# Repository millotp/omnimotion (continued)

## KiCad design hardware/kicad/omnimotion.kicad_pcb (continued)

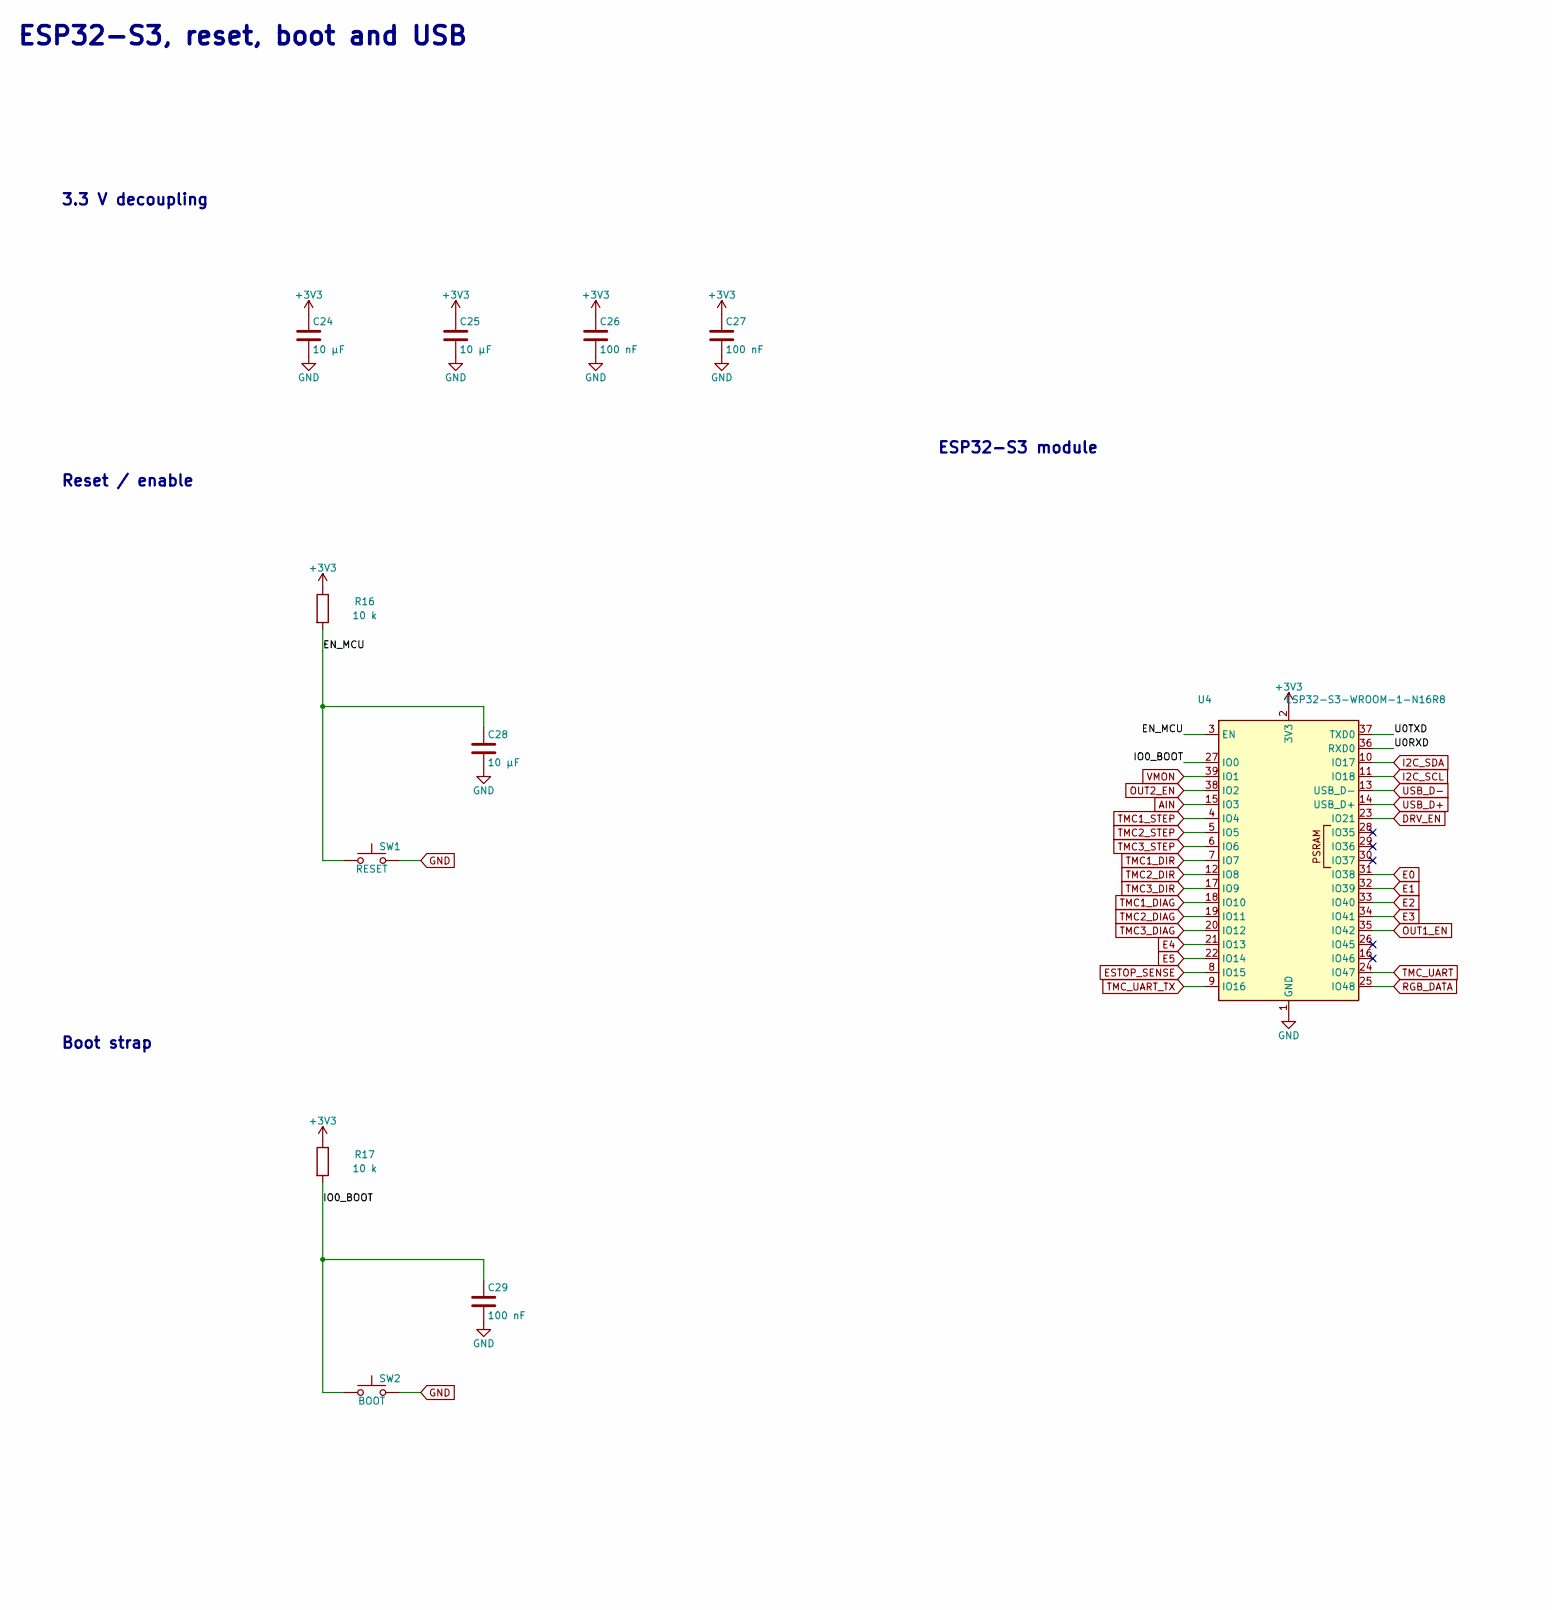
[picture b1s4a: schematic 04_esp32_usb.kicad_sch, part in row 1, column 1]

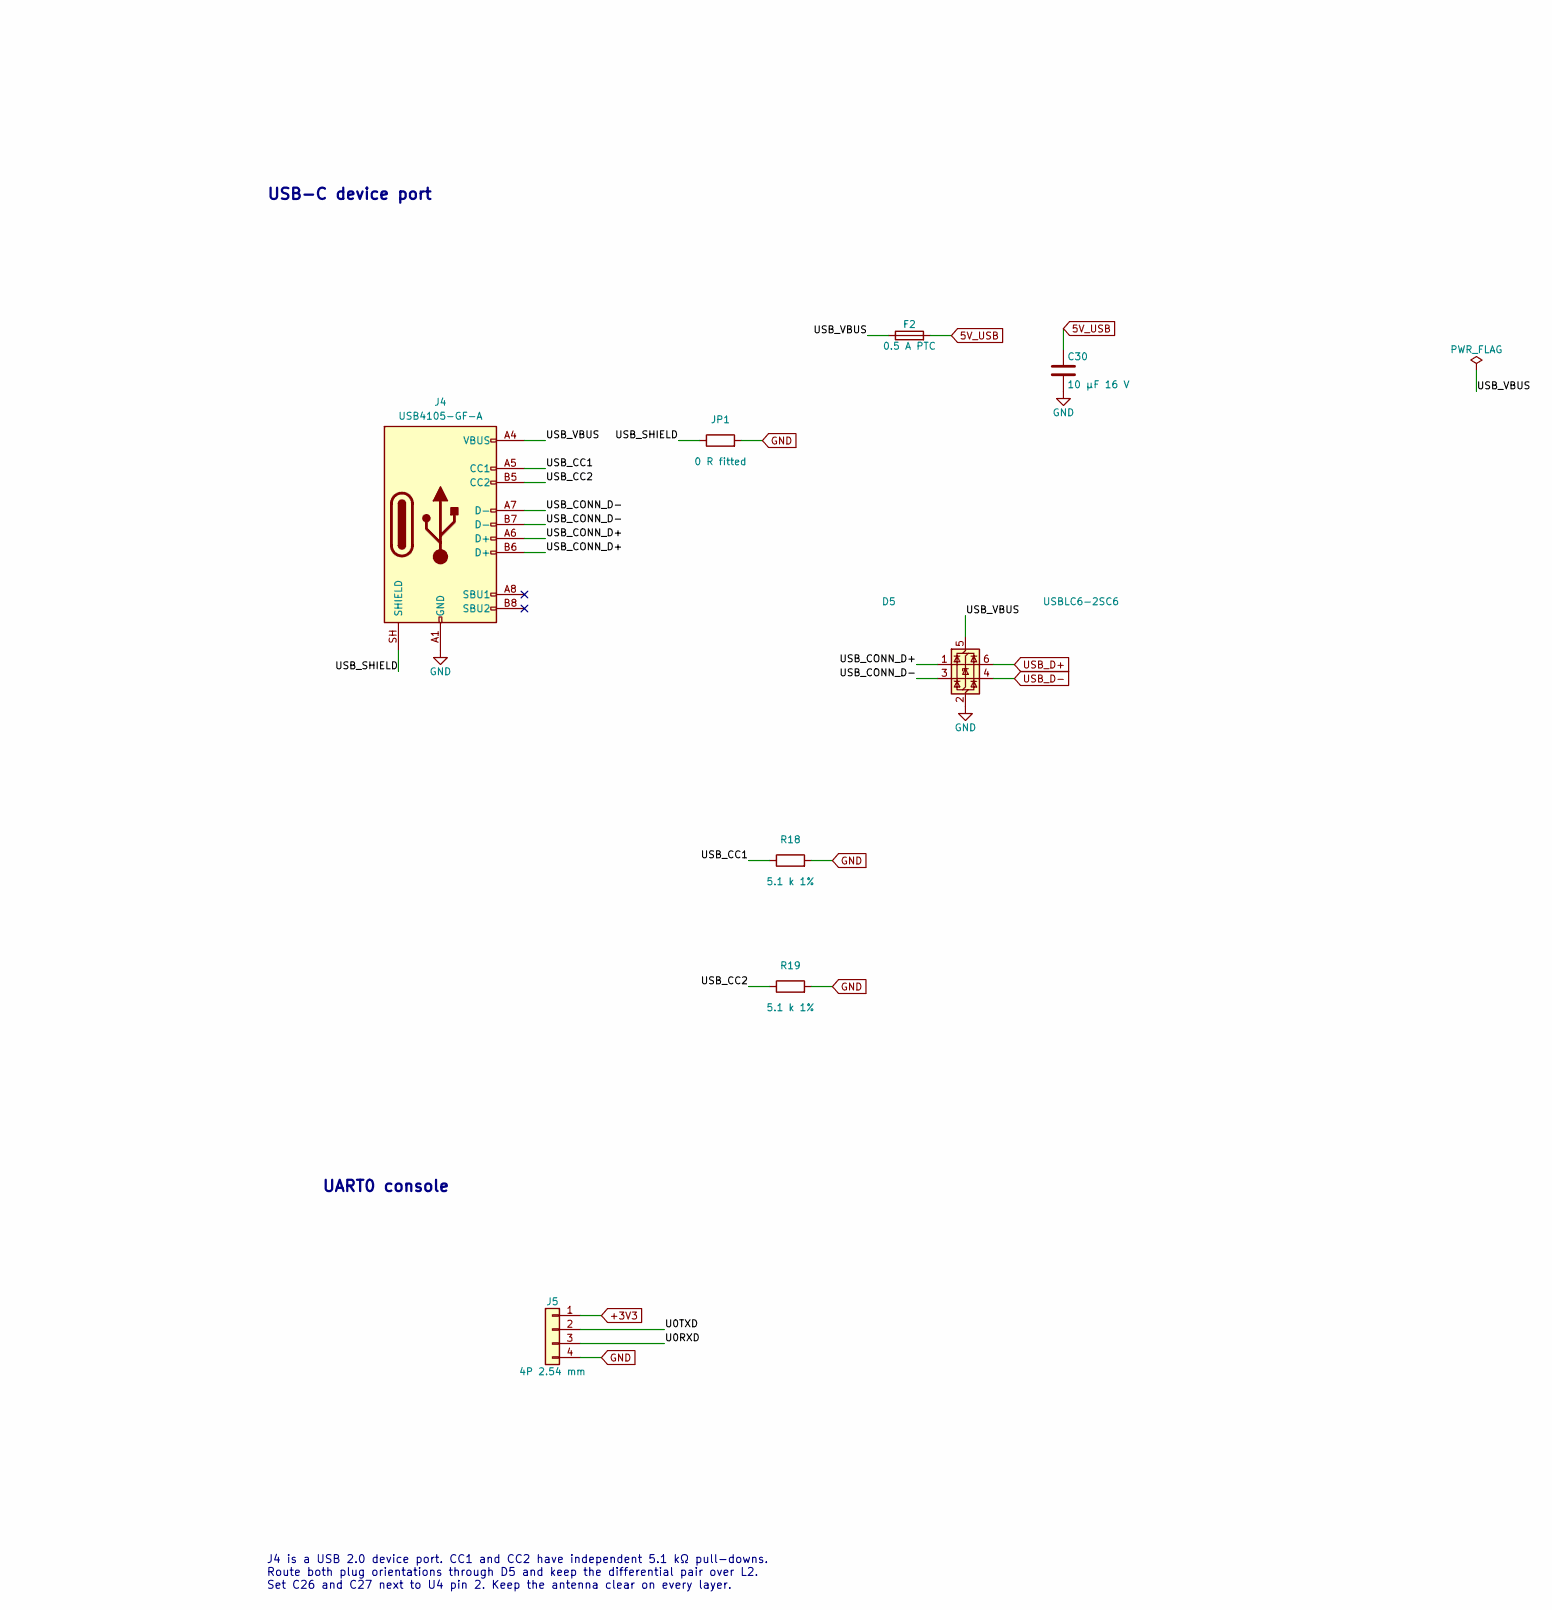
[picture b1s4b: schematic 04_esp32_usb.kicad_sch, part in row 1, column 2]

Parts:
C24, C25, C28: 10 µF; C_0805_2012Metric
C26, C27, C29: 100 nF; C_0603_1608Metric
C30: 10 µF 16 V; C_0805_2012Metric
D5: USBLC6-2SC6; SOT-23-6
F2: 0.5 A PTC; Fuse_1206_3216Metric
J4: USB4105-GF-A; USB_C_Receptacle_GCT_USB4105-xx-A_16P_TopMnt_Horizontal
J5: 4P 2.54 mm; PinHeader_1x04_P2.54mm_Vertical
JP1: 0 R fitted; R_0603_1608Metric
R16, R17: 10 k; R_0603_1608Metric
R18, R19: 5.1 k 1%; R_0603_1608Metric
SW1: RESET; SW_SPST_CK_RS282G05A3
SW2: BOOT; SW_SPST_CK_RS282G05A3
U4: ESP32-S3-WROOM-1-N16R8; ESP32-S3-WROOM-1

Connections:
5V_USB: C30.1, F2.2; also elsewhere on the board
+3V3: C24.1, C25.1, C26.1, C27.1, J5.1, R16.1, R17.1, U4.2 (3V3); also elsewhere on the board
/ESP32-S3 and native USB/EN_MCU: C28.1, R16.2, SW1.1, U4.3 (EN)
/ESP32-S3 and native USB/IO0_BOOT: C29.1, R17.2, SW2.1, U4.27 (IO0)
/ESP32-S3 and native USB/U0RXD: J5.3, U4.36 (RXD0)
/ESP32-S3 and native USB/U0TXD: J5.2, U4.37 (TXD0)
/ESP32-S3 and native USB/USB_CC1: J4.A5 (CC1), R18.1
/ESP32-S3 and native USB/USB_CC2: J4.B5 (CC2), R19.1
/ESP32-S3 and native USB/USB_CONN_D+: D5.1 (I/O1), J4.A6 (D+), J4.B6 (D+)
/ESP32-S3 and native USB/USB_CONN_D-: D5.3 (I/O2), J4.A7 (D-), J4.B7 (D-)
/ESP32-S3 and native USB/USB_SHIELD: J4.SH (SHIELD), JP1.1
/ESP32-S3 and native USB/USB_VBUS: D5.5 (VBUS), F2.1, J4.A4 (VBUS), J4.A9 (VBUS), J4.B4 (VBUS), J4.B9 (VBUS)
AIN: U4.15 (IO3); also elsewhere on the board
DRV_EN: U4.23 (IO21); also elsewhere on the board
E0: U4.31 (IO38); also elsewhere on the board
E1: U4.32 (IO39); also elsewhere on the board
E2: U4.33 (IO40); also elsewhere on the board
E3: U4.34 (IO41); also elsewhere on the board
E4: U4.21 (IO13); also elsewhere on the board
E5: U4.22 (IO14); also elsewhere on the board
ESTOP_SENSE: U4.8 (IO15); also elsewhere on the board
GND: C24.2, C25.2, C26.2, C27.2, C28.2, C29.2, C30.2, D5.2 (GND), J4.A1 (GND), J4.A12 (GND), J4.B1 (GND), J4.B12 (GND), J5.4, JP1.2, R18.2, R19.2, SW1.2, SW2.2, U4.1 (GND), U4.40 (GND), U4.41 (GND); also elsewhere on the board
I2C_SCL: U4.11 (IO18); also elsewhere on the board
I2C_SDA: U4.10 (IO17); also elsewhere on the board
OUT1_EN: U4.35 (IO42); also elsewhere on the board
OUT2_EN: U4.38 (IO2); also elsewhere on the board
RGB_DATA: U4.25 (IO48); also elsewhere on the board
TMC1_DIAG: U4.18 (IO10); also elsewhere on the board
TMC1_DIR: U4.7 (IO7); also elsewhere on the board
TMC1_STEP: U4.4 (IO4); also elsewhere on the board
TMC2_DIAG: U4.19 (IO11); also elsewhere on the board
TMC2_DIR: U4.12 (IO8); also elsewhere on the board
TMC2_STEP: U4.5 (IO5); also elsewhere on the board
TMC3_DIAG: U4.20 (IO12); also elsewhere on the board
TMC3_DIR: U4.17 (IO9); also elsewhere on the board
TMC3_STEP: U4.6 (IO6); also elsewhere on the board
TMC_UART: U4.24 (IO47); also elsewhere on the board
TMC_UART_TX: U4.9 (IO16); also elsewhere on the board
USB_D+: D5.6 (I/O1), U4.14 (USB_D+); also elsewhere on the board
USB_D-: D5.4 (I/O2), U4.13 (USB_D-); also elsewhere on the board
VMON: U4.39 (IO1); also elsewhere on the board

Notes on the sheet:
ESP32-S3, reset, boot and USB
3.3 V decoupling
Reset / enable
Boot strap
ESP32-S3 module
USB-C device port
UART0 console
J4 is a USB 2.0 device port. CC1 and CC2 have independent 5.1 kΩ pull-downs. Route both plug orientations through D5 and keep the differential pair over L2. Set C26 and C27 next to U4 pin 2. Keep the antenna clear on every layer.

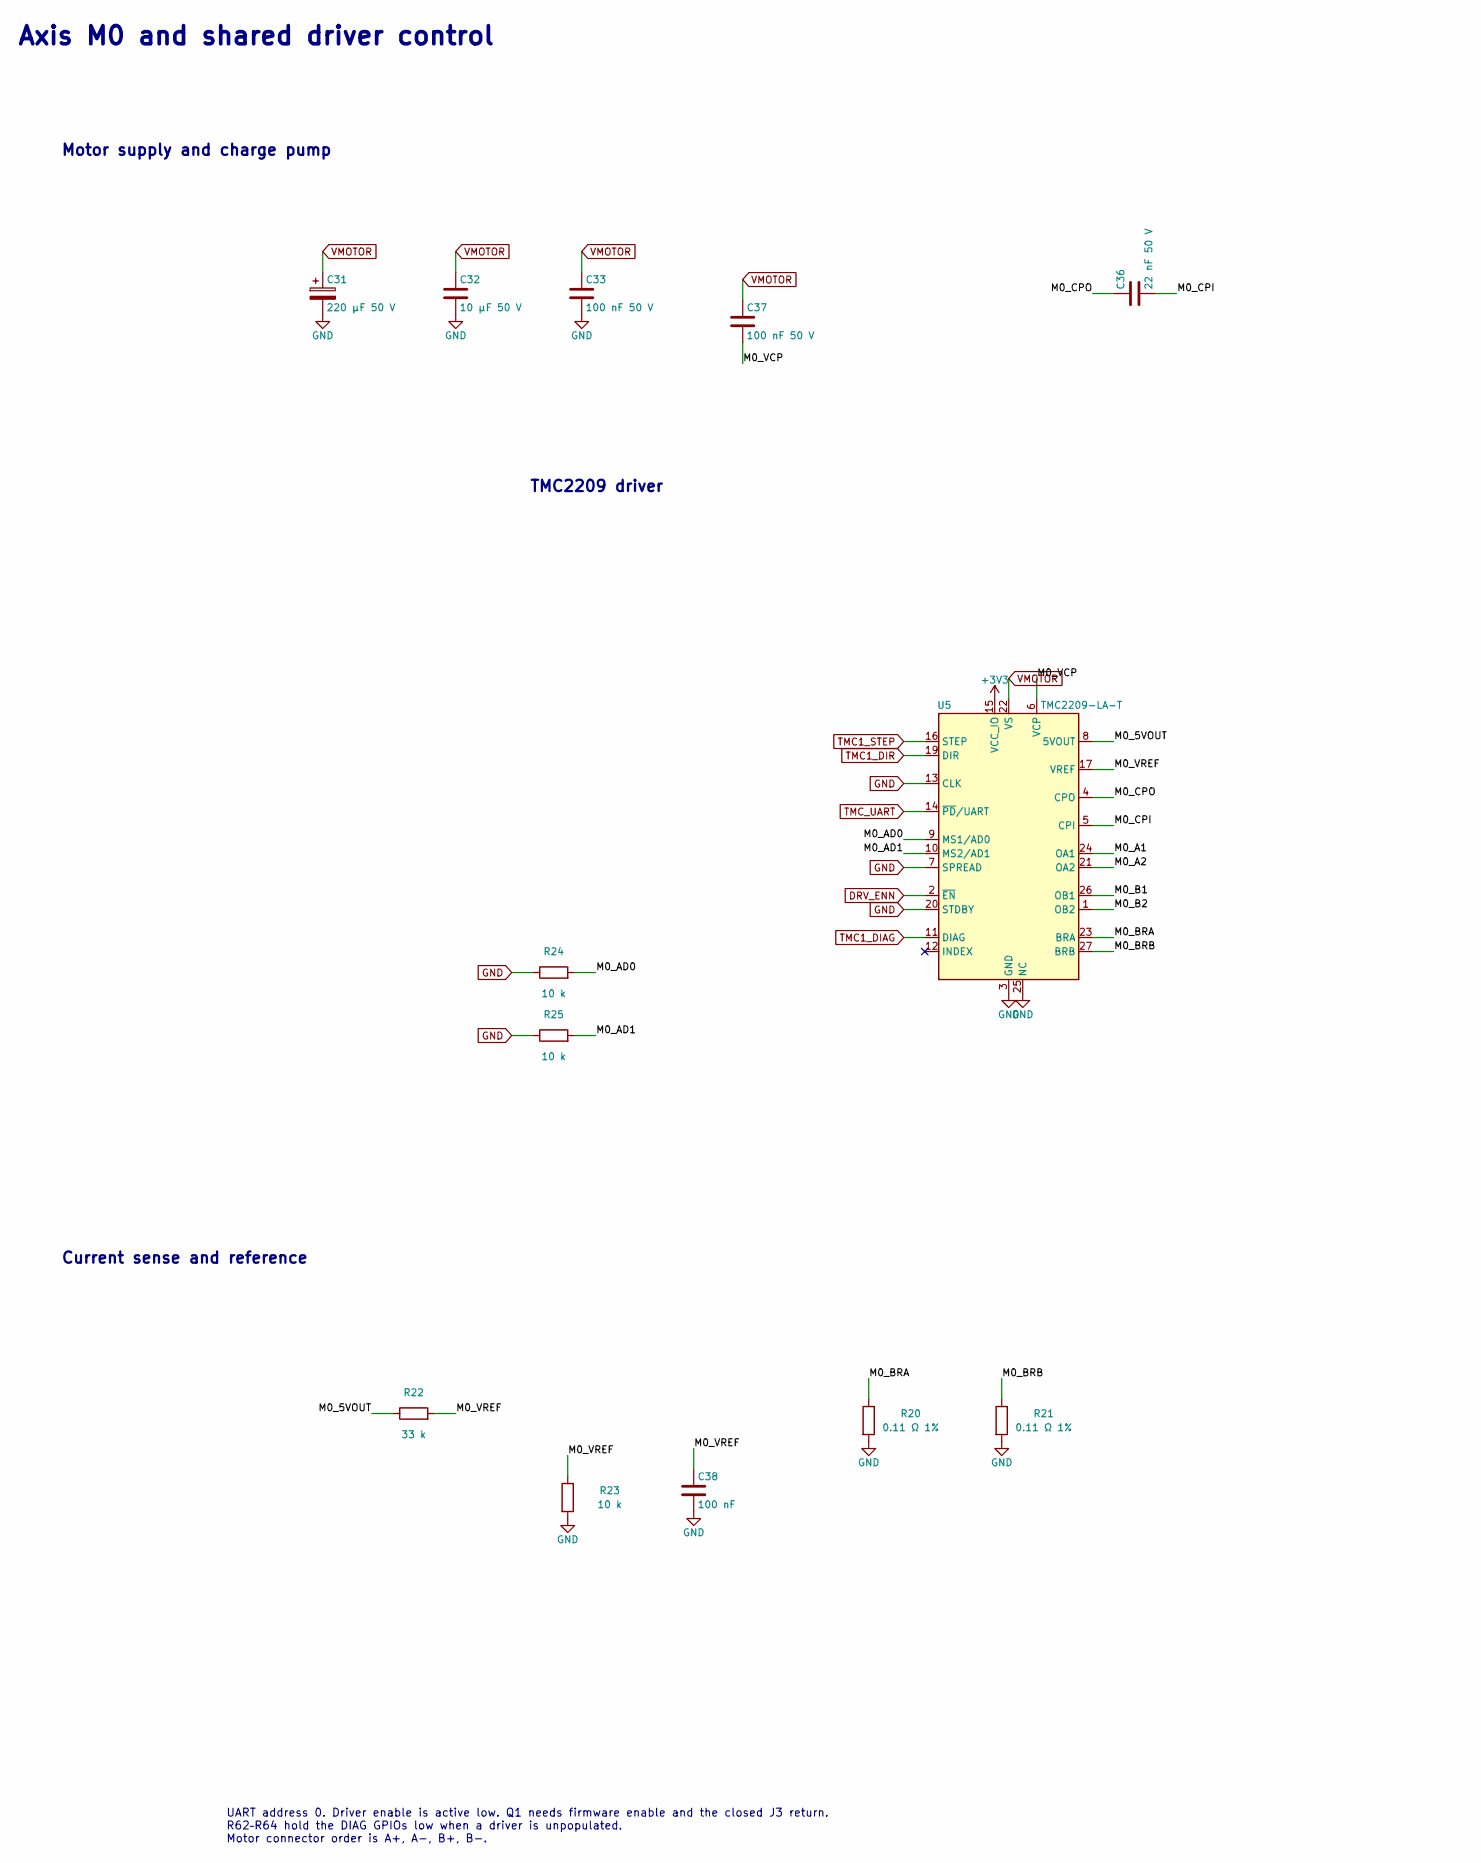
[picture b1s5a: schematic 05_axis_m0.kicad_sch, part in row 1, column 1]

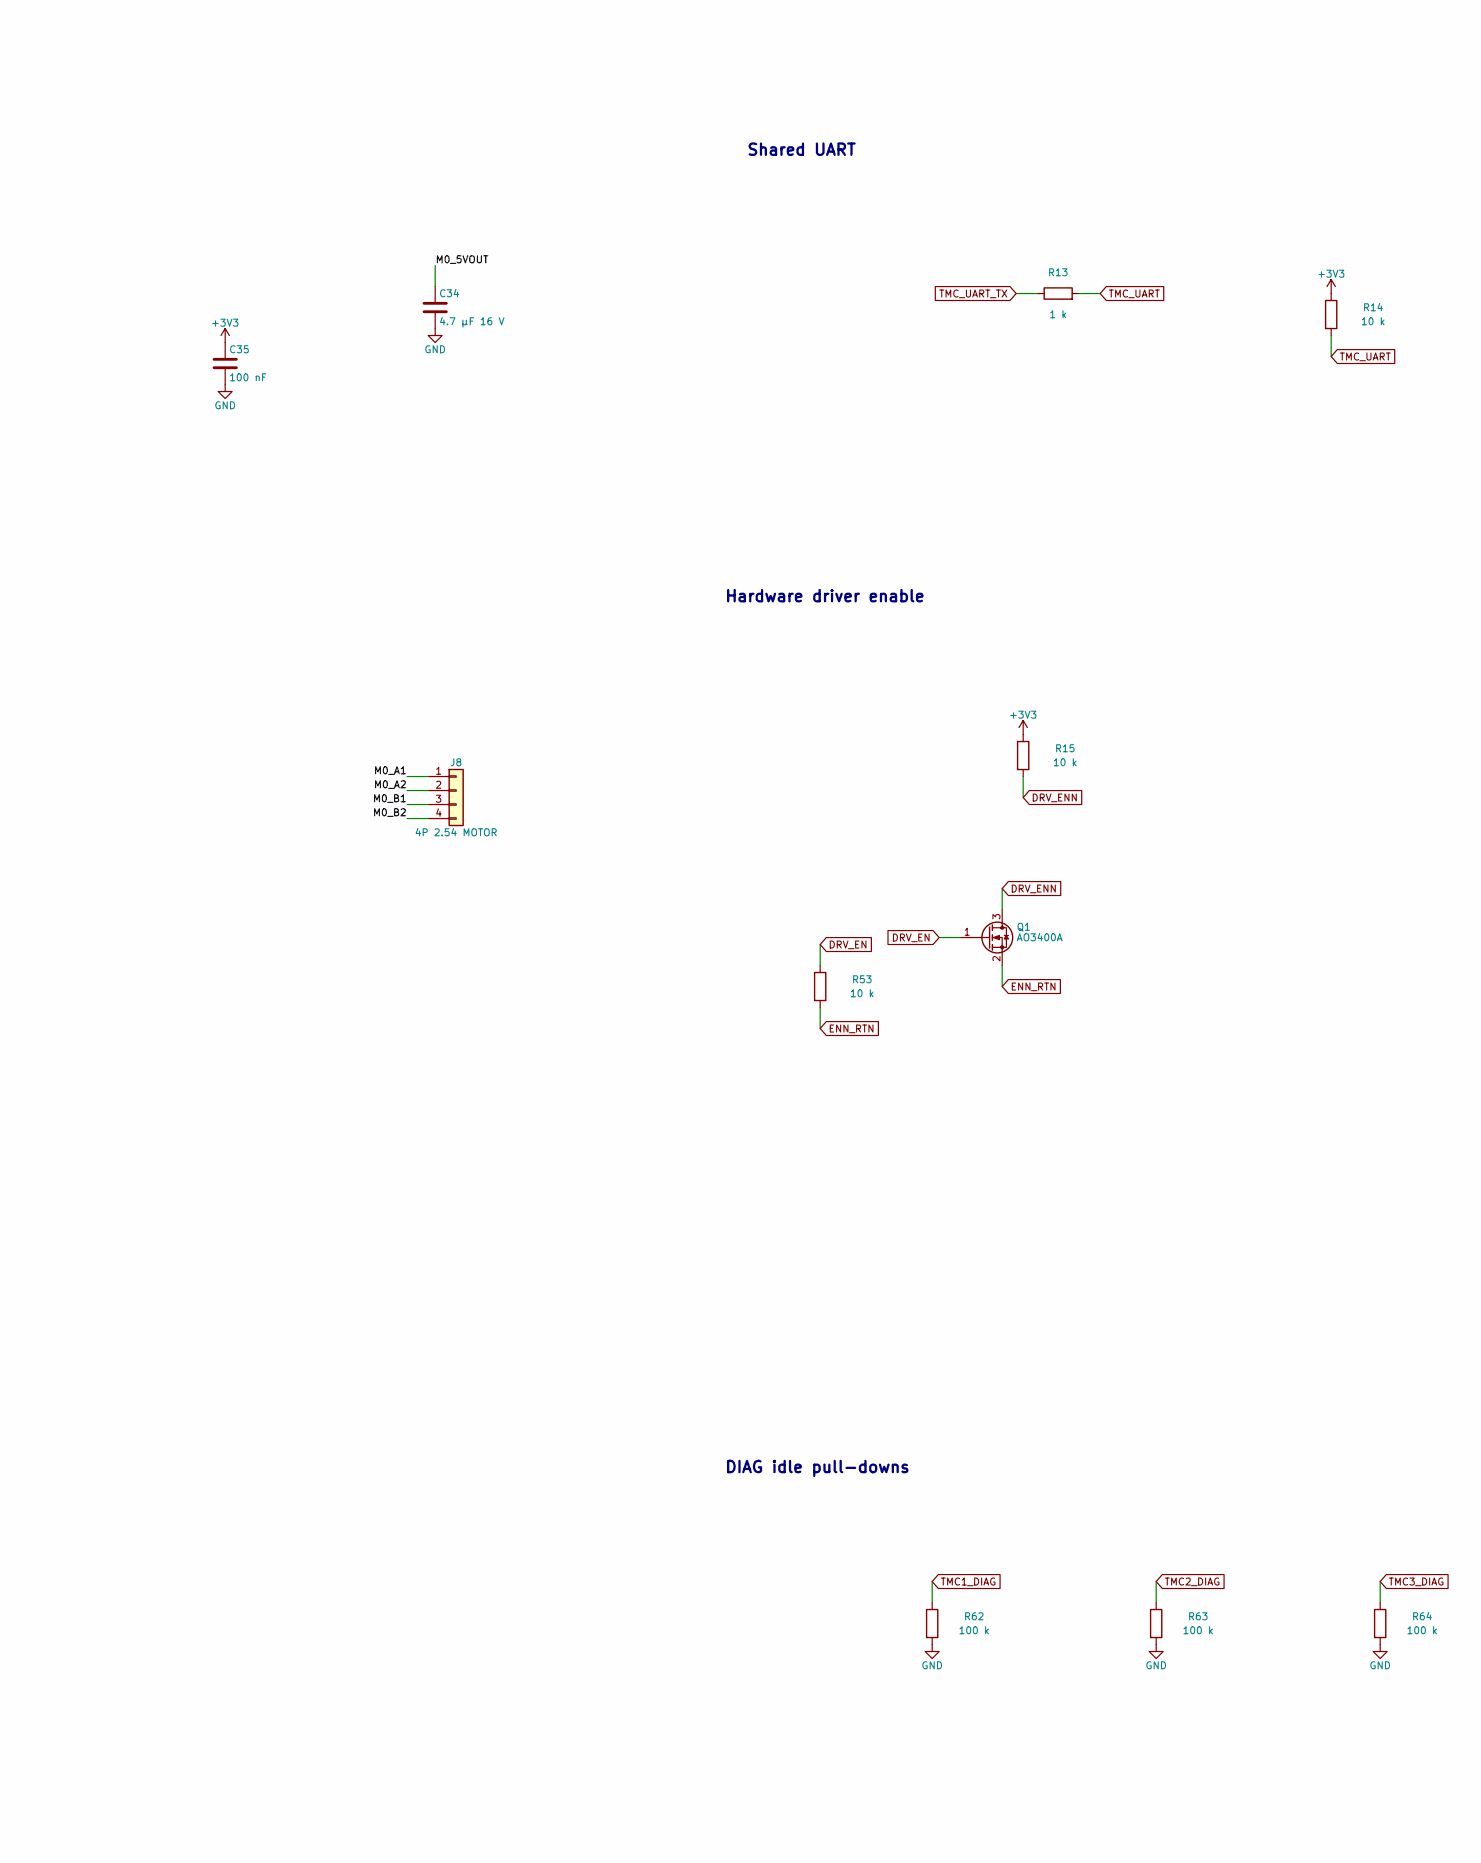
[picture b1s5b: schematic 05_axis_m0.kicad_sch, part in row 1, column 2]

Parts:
C31: 220 µF 50 V; CP_Elec_10x10.5
C32: 10 µF 50 V; C_1210_3225Metric
C33, C37: 100 nF 50 V; C_0603_1608Metric
C34: 4.7 µF 16 V; C_0603_1608Metric
C35, C38: 100 nF; C_0603_1608Metric
C36: 22 nF 50 V; C_0603_1608Metric
J8: 4P 2.54 MOTOR; PinHeader_1x04_P2.54mm_Vertical
Q1: AO3400A; SOT-23
R13: 1 k; R_0603_1608Metric
R14, R15, R23, R24, R25, R53: 10 k; R_0603_1608Metric
R20, R21: 0.11 Ω 1%; R_2512_6332Metric
R22: 33 k; R_0603_1608Metric
R62, R63, R64: 100 k; R_0603_1608Metric
U5: TMC2209-LA-T; TMC2209_VQFN28_ThermalVias_0.3mm

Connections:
+3V3: C35.1, R14.1, R15.1, U5.15 (VCC_IO); also elsewhere on the board
/Axis M0 - UART address 0/M0_5VOUT: C34.1, R22.1, U5.8 (5VOUT)
/Axis M0 - UART address 0/M0_A1: J8.1, U5.24 (OA1)
/Axis M0 - UART address 0/M0_A2: J8.2, U5.21 (OA2)
/Axis M0 - UART address 0/M0_AD0: R24.2, U5.9 (MS1/AD0)
/Axis M0 - UART address 0/M0_AD1: R25.2, U5.10 (MS2/AD1)
/Axis M0 - UART address 0/M0_B1: J8.3, U5.26 (OB1)
/Axis M0 - UART address 0/M0_B2: J8.4, U5.1 (OB2)
/Axis M0 - UART address 0/M0_BRA: R20.1, U5.23 (BRA)
/Axis M0 - UART address 0/M0_BRB: R21.1, U5.27 (BRB)
/Axis M0 - UART address 0/M0_CPI: C36.2, U5.5 (CPI)
/Axis M0 - UART address 0/M0_CPO: C36.1, U5.4 (CPO)
/Axis M0 - UART address 0/M0_VCP: C37.2, U5.6 (VCP)
/Axis M0 - UART address 0/M0_VREF: C38.1, R22.2, R23.1, U5.17 (VREF)
DRV_EN: Q1.1 (G), R53.1; also elsewhere on the board
DRV_ENN: Q1.3 (D), R15.2, U5.2 (~EN); also elsewhere on the board
ENN_RTN: Q1.2 (S), R53.2; also elsewhere on the board
GND: C31.2, C32.2, C33.2, C34.2, C35.2, C38.2, R20.2, R21.2, R23.2, R24.1, R25.1, R62.2, R63.2, R64.2, U5.3 (GND), U5.7 (SPREAD), U5.13 (CLK), U5.18 (GND), U5.20 (STDBY), U5.25 (NC), U5.29 (GND); also elsewhere on the board
TMC1_DIAG: R62.1, U5.11 (DIAG); also elsewhere on the board
TMC1_DIR: U5.19 (DIR); also elsewhere on the board
TMC1_STEP: U5.16 (STEP); also elsewhere on the board
TMC2_DIAG: R63.1; also elsewhere on the board
TMC3_DIAG: R64.1; also elsewhere on the board
TMC_UART: R13.2, R14.2, U5.14 (~PD/UART); also elsewhere on the board
TMC_UART_TX: R13.1; also elsewhere on the board
VMOTOR: C31.1, C32.1, C33.1, C37.1, U5.22 (VS), U5.28 (VS); also elsewhere on the board

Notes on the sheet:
Shared UART
TMC2209 driver
Axis M0 and shared driver control
Motor supply and charge pump
UART address 0. Driver enable is active low. Q1 needs firmware enable and the closed J3 return. R62–R64 hold the DIAG GPIOs low when a driver is unpopulated. Motor connector order is A+, A−, B+, B−.
Hardware driver enable
DIAG idle pull-downs
Current sense and reference

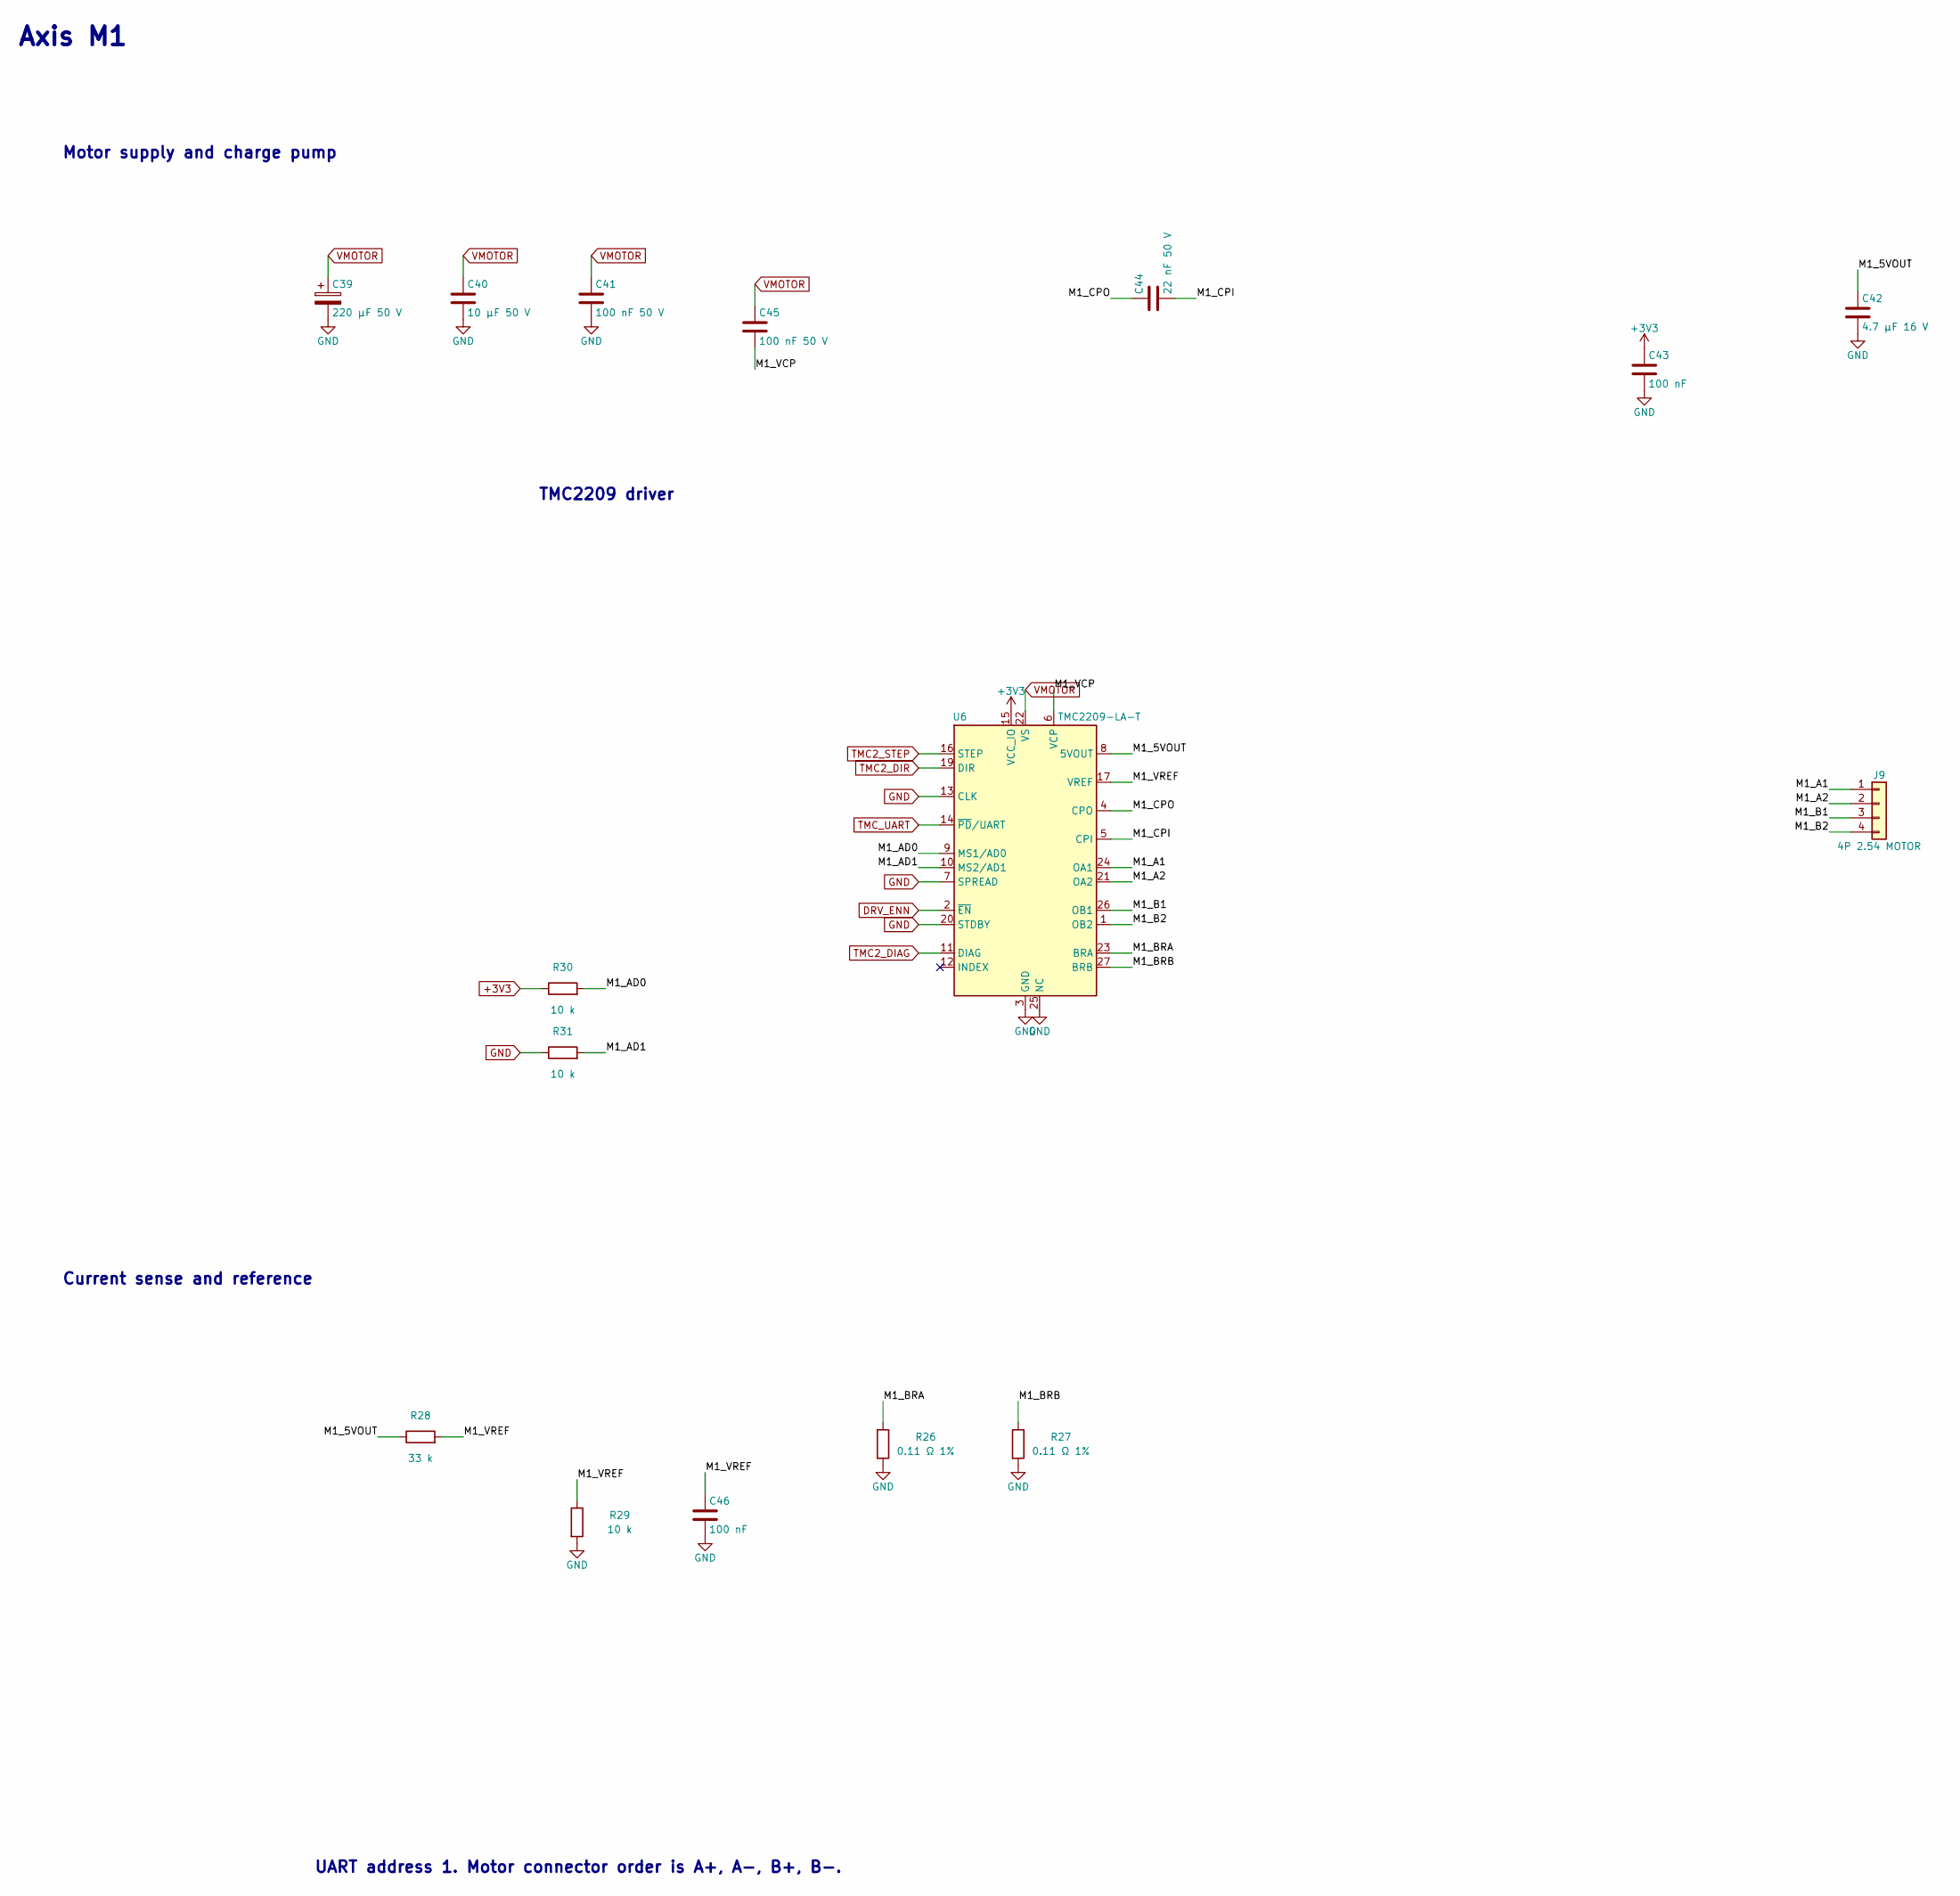
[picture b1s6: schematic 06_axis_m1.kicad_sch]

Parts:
C39: 220 µF 50 V; CP_Elec_10x10.5
C40: 10 µF 50 V; C_1210_3225Metric
C41, C45: 100 nF 50 V; C_0603_1608Metric
C42: 4.7 µF 16 V; C_0603_1608Metric
C43, C46: 100 nF; C_0603_1608Metric
C44: 22 nF 50 V; C_0603_1608Metric
J9: 4P 2.54 MOTOR; PinHeader_1x04_P2.54mm_Vertical
R26, R27: 0.11 Ω 1%; R_2512_6332Metric
R28: 33 k; R_0603_1608Metric
R29, R30, R31: 10 k; R_0603_1608Metric
U6: TMC2209-LA-T; TMC2209_VQFN28_ThermalVias_0.3mm

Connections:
+3V3: C43.1, R30.1, U6.15 (VCC_IO); also elsewhere on the board
/Axis M1 - UART address 1/M1_5VOUT: C42.1, R28.1, U6.8 (5VOUT)
/Axis M1 - UART address 1/M1_A1: J9.1, U6.24 (OA1)
/Axis M1 - UART address 1/M1_A2: J9.2, U6.21 (OA2)
/Axis M1 - UART address 1/M1_AD0: R30.2, U6.9 (MS1/AD0)
/Axis M1 - UART address 1/M1_AD1: R31.2, U6.10 (MS2/AD1)
/Axis M1 - UART address 1/M1_B1: J9.3, U6.26 (OB1)
/Axis M1 - UART address 1/M1_B2: J9.4, U6.1 (OB2)
/Axis M1 - UART address 1/M1_BRA: R26.1, U6.23 (BRA)
/Axis M1 - UART address 1/M1_BRB: R27.1, U6.27 (BRB)
/Axis M1 - UART address 1/M1_CPI: C44.2, U6.5 (CPI)
/Axis M1 - UART address 1/M1_CPO: C44.1, U6.4 (CPO)
/Axis M1 - UART address 1/M1_VCP: C45.2, U6.6 (VCP)
/Axis M1 - UART address 1/M1_VREF: C46.1, R28.2, R29.1, U6.17 (VREF)
DRV_ENN: U6.2 (~EN); also elsewhere on the board
GND: C39.2, C40.2, C41.2, C42.2, C43.2, C46.2, R26.2, R27.2, R29.2, R31.1, U6.3 (GND), U6.7 (SPREAD), U6.13 (CLK), U6.18 (GND), U6.20 (STDBY), U6.25 (NC), U6.29 (GND); also elsewhere on the board
TMC2_DIAG: U6.11 (DIAG); also elsewhere on the board
TMC2_DIR: U6.19 (DIR); also elsewhere on the board
TMC2_STEP: U6.16 (STEP); also elsewhere on the board
TMC_UART: U6.14 (~PD/UART); also elsewhere on the board
VMOTOR: C39.1, C40.1, C41.1, C45.1, U6.22 (VS), U6.28 (VS); also elsewhere on the board

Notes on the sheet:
Current sense and reference
Axis M1
UART address 1. Motor connector order is A+, A−, B+, B−.
Motor supply and charge pump
TMC2209 driver
